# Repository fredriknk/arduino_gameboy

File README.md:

# ARDUINO-GAMEBOY

INFO INFO

[SCHEMATIC](./DOCUMENTATION/arduino_gameboy-Schematic.pdf)

[Assembly IBOM](https://htmlpreview.github.io/?https://raw.githubusercontent.com/fredriknk/arduino_gameboy/main/DOCUMENTATION/arduino_gameboy-ibom.html)

## FRONT

## BACK

## EXTRA INFO

INFO INFO

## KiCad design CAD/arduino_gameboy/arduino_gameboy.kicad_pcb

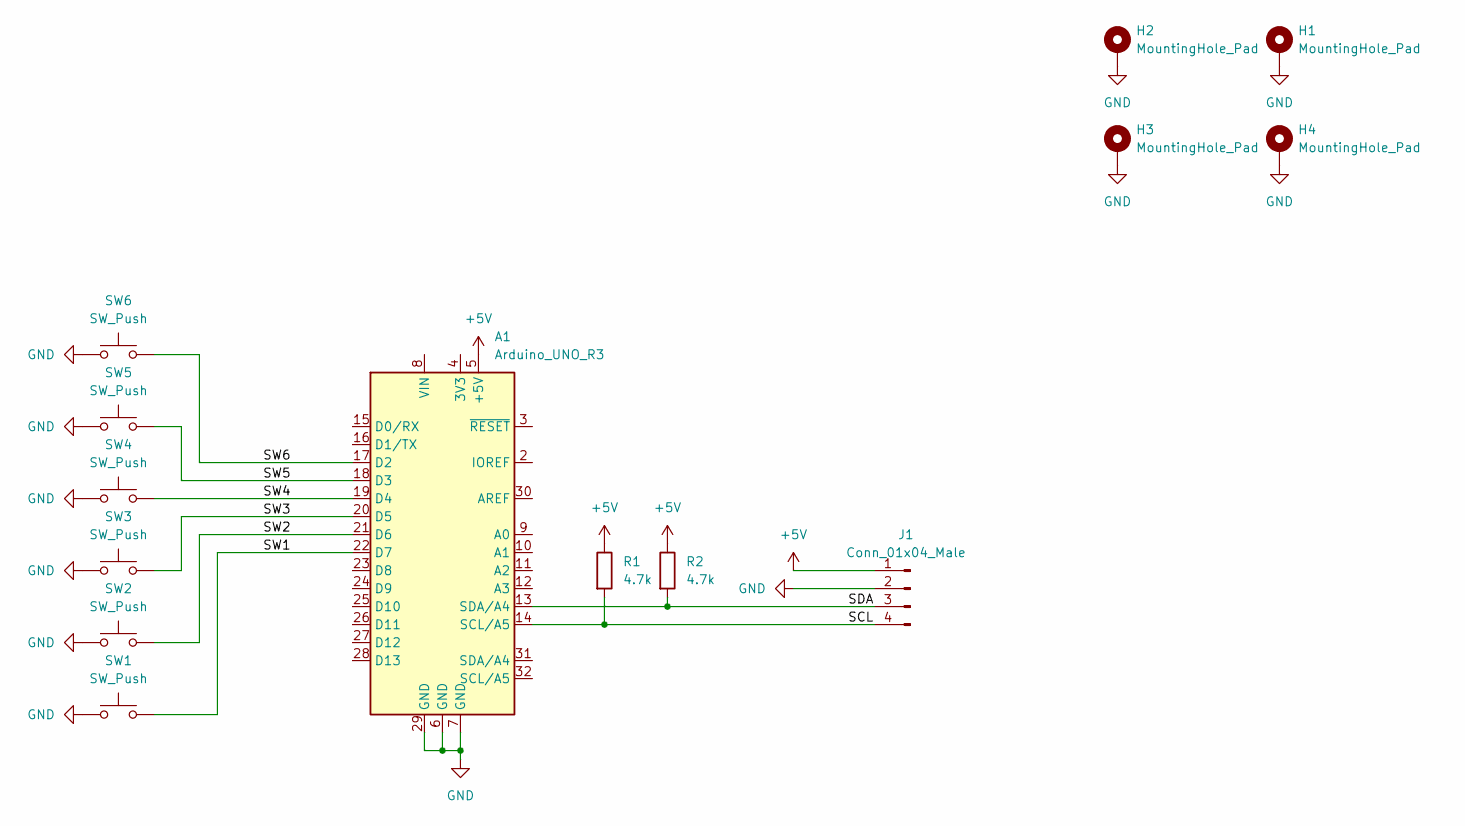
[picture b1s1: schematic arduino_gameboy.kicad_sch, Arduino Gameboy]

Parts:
A1: Arduino_UNO_R3
H1, H2, H3, H4: MountingHole_Pad; MountingHole_3.2mm_M3_Pad_Via
J1: Conn_01x04_Male; PinHeader_1x04_P2.54mm_Vertical
R1, R2: 4.7k; R_Axial_DIN0204_L3.6mm_D1.6mm_P7.62mm_Horizontal
SW1, SW2, SW3, SW4, SW5, SW6: SW_Push; SW_PUSH-12mm

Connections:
+5V: A1.5 (+5V), J1.1, R1.1, R2.1
/SCL: A1.14 (SCL/A5), J1.4, R1.2
/SDA: A1.13 (SDA/A4), J1.3, R2.2
/SW1: A1.22 (D7), SW1.1
/SW2: A1.21 (D6), SW2.1
/SW3: A1.20 (D5), SW3.1
/SW4: A1.19 (D4), SW4.1
/SW5: A1.18 (D3), SW5.1
/SW6: A1.17 (D2), SW6.1
GND: A1.6 (GND), A1.7 (GND), A1.29 (GND), H1.1, H2.1, H3.1, H4.1, J1.2, SW1.2, SW2.2, SW3.2, SW4.2, SW5.2, SW6.2

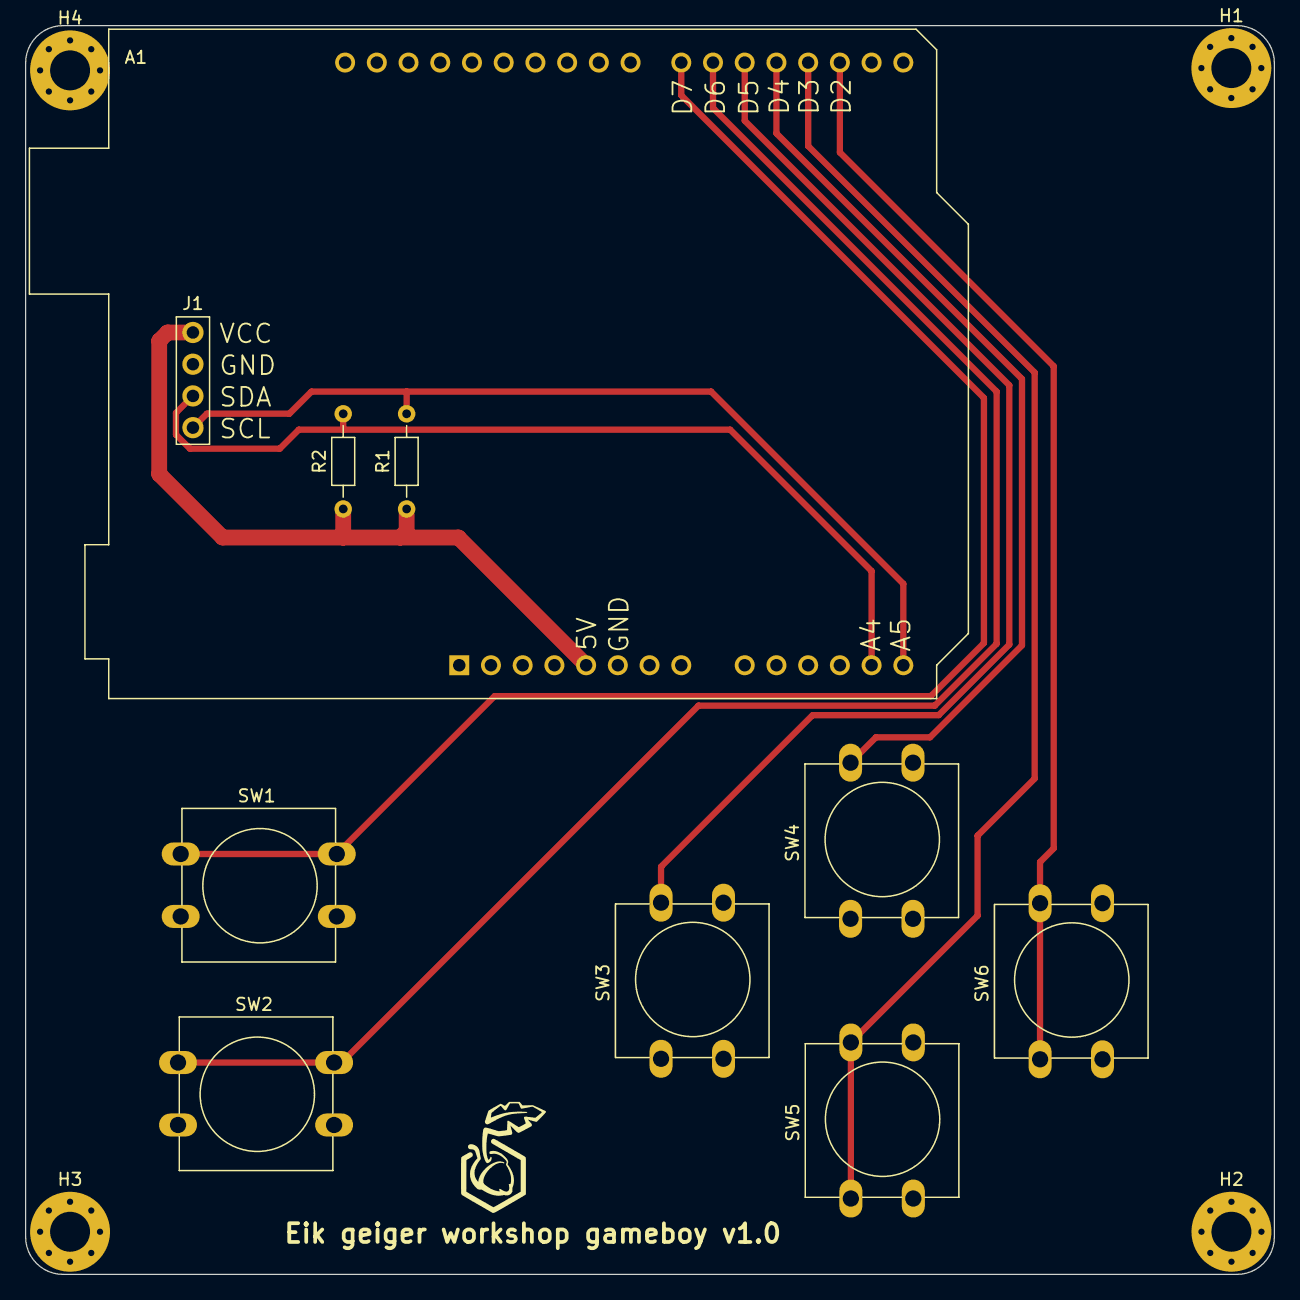
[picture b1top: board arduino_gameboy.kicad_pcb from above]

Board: 2 copper layers, 100.0 x 100.0 mm, 14 parts (0 on the bottom side), 10 nets.

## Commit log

2024-02-12 First Project Push
2024-02-12 Added ibom link
2024-02-12 Ibom update
2024-02-12 Update LICENSE
